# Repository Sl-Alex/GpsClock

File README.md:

#LED matrix GPS wall clock

This project has the following features:
- 80x24 big LED matrix display with automatic brightness control (based on HT16K33 drivers).
- Temperature/humidity measurement.
- Air pressure monitoring/logging. Last 24 hours are always on the display in a form of a diagram.
- Non-volatile FRAM memory for the air pressure log.
- GPS module for automatic time synchronization.
- No buttons, no settings. User manual is not required.
- Automatic DST time correction. Time zone can be easily changed in the source code, no further modifications are required.

Following 3rd party HW was used:
- STM32F103C8T6 minimum system development board ([photo](./modules/stm32f103c8t6_board.jpg))
- BMP180 temperature/pressure sensor module ([photo](./modules/bmp180_module.jpg))
- BH1750 light sensor  module ([photo](./modules/bh1750_module.jpg))
- Si7021 temperature/humidity sensor  module ([photo](./modules/si7021_module.jpg))
- FM24C04 FRAM chip.
- EB-800 GPS module with 5V->3V converter.

Module interconnections are available on [this](./schematic.png) diagram. The only PCB you have to make is a HT16K33 module (15 pcs). KiCAD project is in the [PCB](./PCB) folder.

P.S. If 32kHz generation on the processor board is not stable, then it is highly recommended to make a proper crystal grounding.

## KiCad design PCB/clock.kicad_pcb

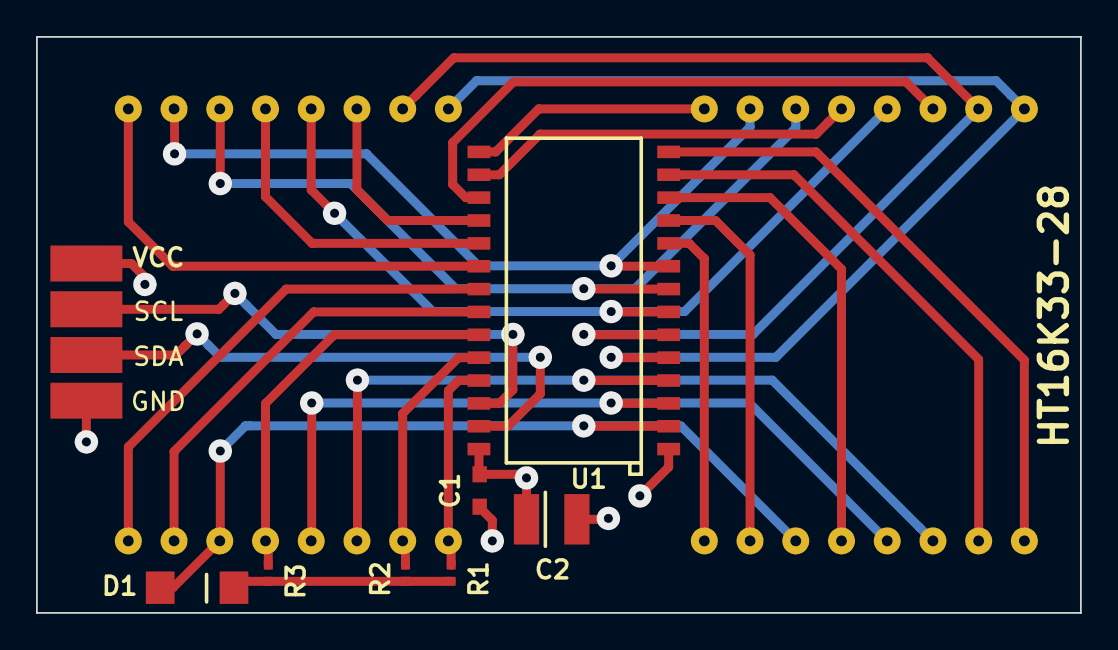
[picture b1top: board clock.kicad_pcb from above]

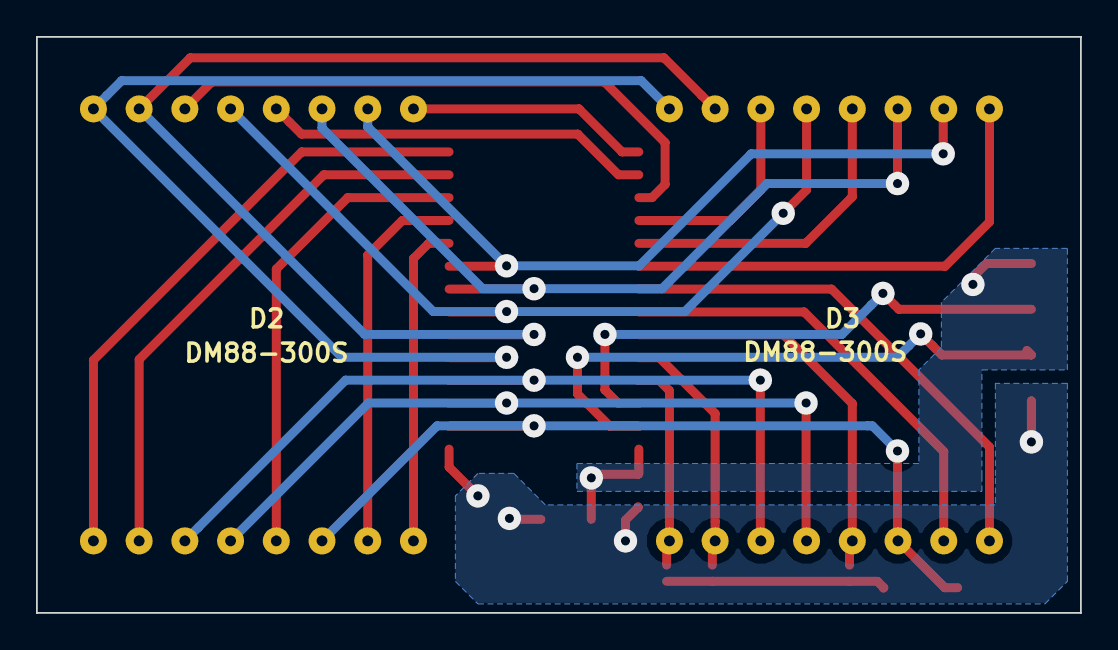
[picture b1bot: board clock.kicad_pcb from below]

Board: 2 copper layers, 58.0 x 32.0 mm, 13 parts (2 on the bottom side), 29 nets.

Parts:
C1: capacitor; 0603_C
C2: capacitor_el; case_B
D1: diode; SOD-80
D2, D3: DM88-300S
R1, R2, R3: resistor; 0402_R
U1: HT16K33-28; SO28
X1: VCC; PLS1_SMD
X2: GND; PLS1_SMD
X3: SCL; PLS1_SMD
X4: SDA; PLS1_SMD

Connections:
/COL0: D1.1, D2.14, D3.14, U1.2
/COL1: D2.12, D3.12, U1.3
/COL2: D2.11, D3.11, U1.4
/COL3: D2.8, D3.8, U1.5
/COL4: D2.7, D3.7, U1.6
/COL5: D2.5, D3.5, U1.7
/COL6: D2.3, D3.3, U1.8
/COL7: D2.2, D3.2, U1.9
/ROW0: D3.9, R1.1, U1.25
/ROW1: D3.10, R2.1, U1.24
/ROW2: D3.13, R3.1, U1.23
/ROW3: D3.15, U1.22
/ROW4: D3.16, U1.21
/ROW5: D3.1, U1.20
/ROW6: D3.4, U1.19
/ROW7: D3.6, U1.18
/ROW8: D2.6, U1.17
/ROW9: D2.4, U1.16
/ROW10: D2.1, U1.15
/ROW11: D2.9, U1.14
/ROW12: D2.10, U1.13
/ROW13: D2.13, U1.12
/ROW14: D2.15, U1.11
/ROW15: D2.16, U1.10
/SCL: U1.26, X3.1
/SDA: U1.27, X4.1
/VCC: C1.1, C2.1, U1.28, X1.1
GND: C1.2, C2.2, U1.1, X2.1
unnamed: D1.2, R1.2, R2.2, R3.2

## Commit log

2016-09-13 First FW public revision
2016-09-13 First public revision of LED matrix driver PCB
2016-09-14 Readme update
2016-09-15 This closes #1 (project finalization)
2016-09-15 Minor description update
2016-09-15 English messages instead of russian (CP1251) will be shown by default.
2016-09-17 Minor schematic correction
